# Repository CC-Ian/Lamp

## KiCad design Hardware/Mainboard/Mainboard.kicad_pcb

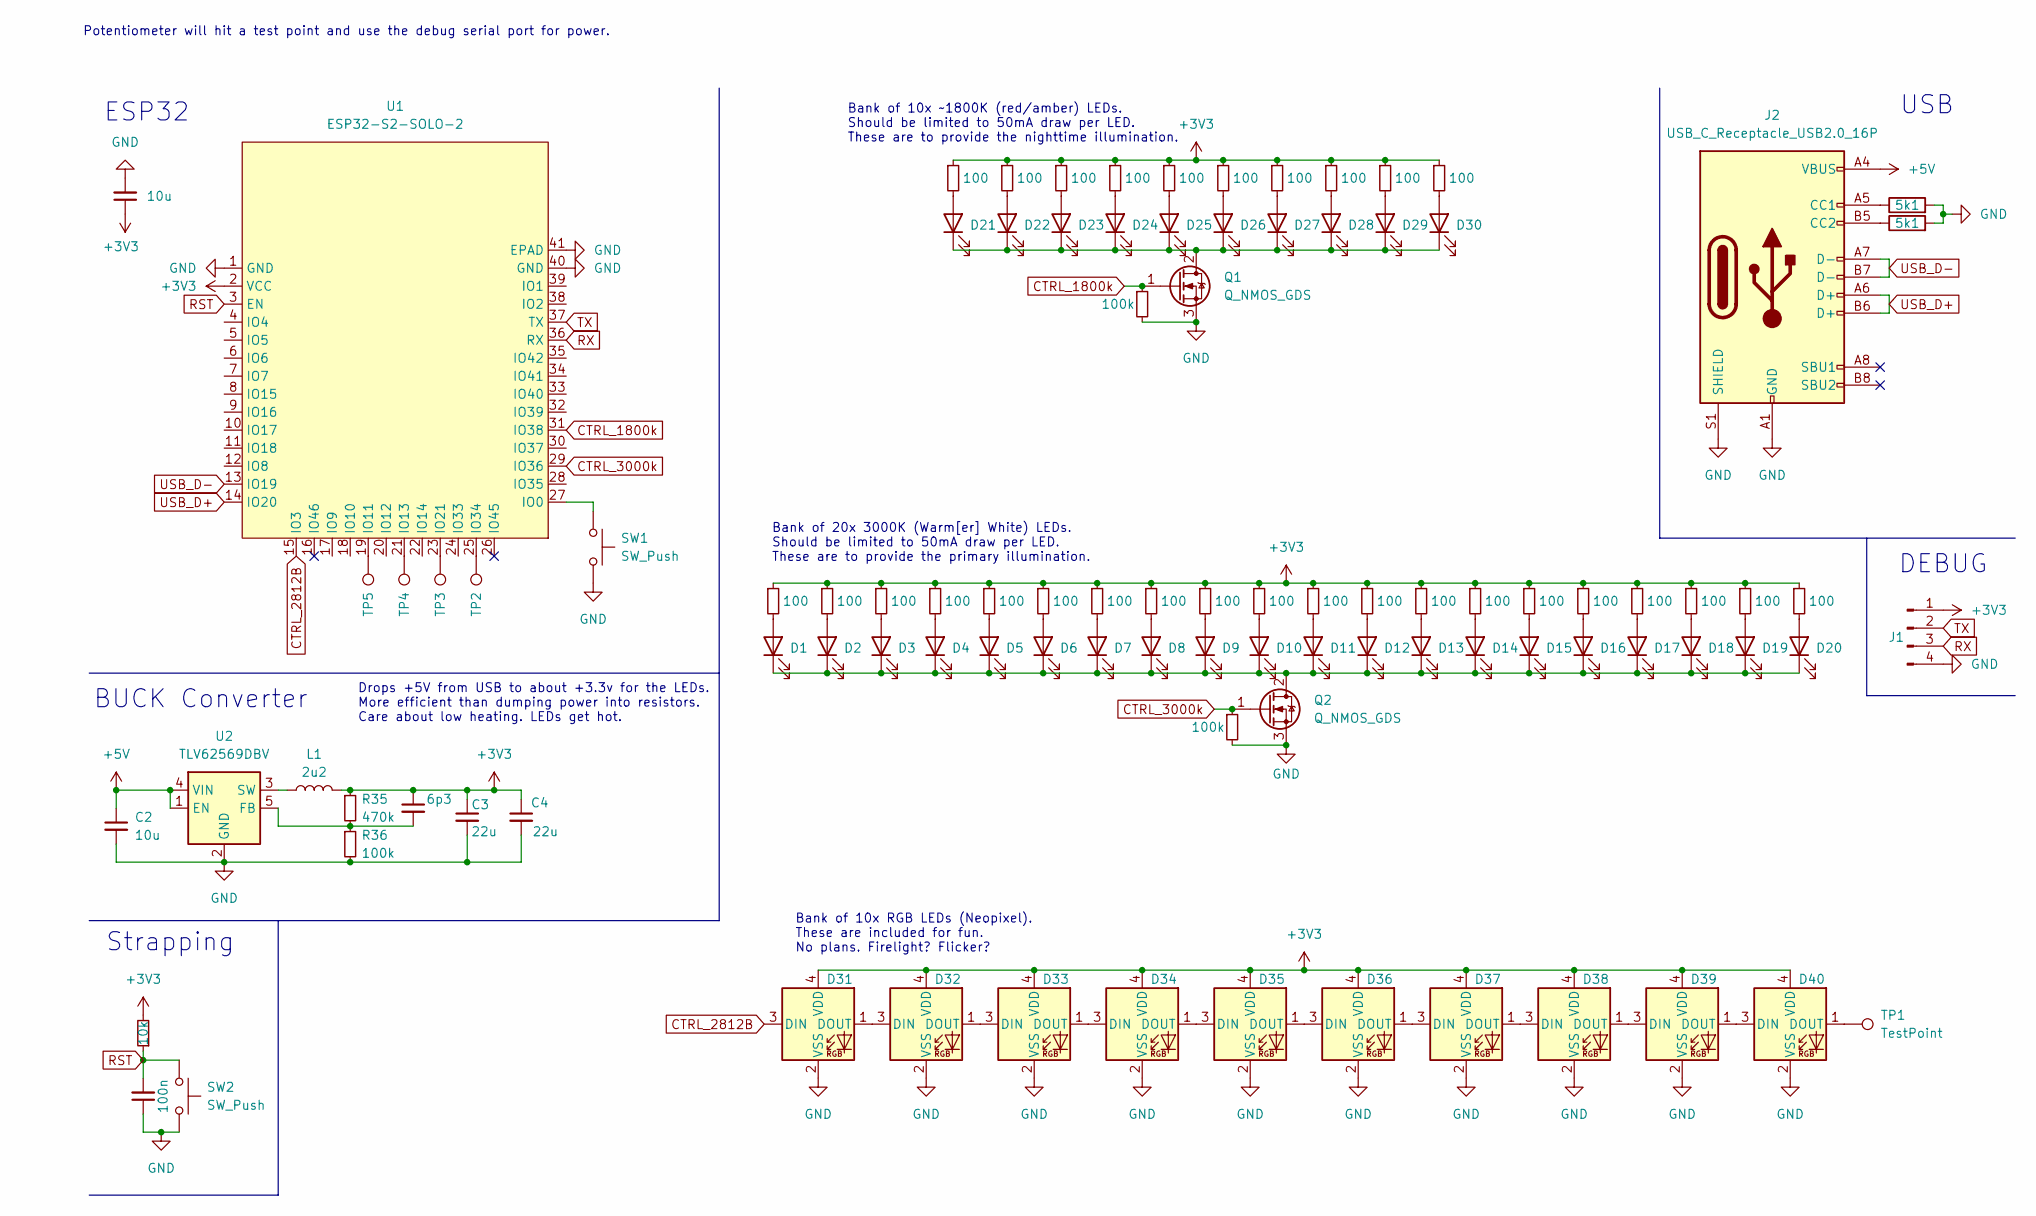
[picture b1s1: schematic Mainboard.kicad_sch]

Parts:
C1: 100n; C_0402_1005Metric
C2, C6: 10u; C_0603_1608Metric
C3, C4: 22u; C_0805_2012Metric
C5: 6p3; C_0402_1005Metric
D1, D2, D3, D4, D5, D6, D7, D8, D9, D10, D11, D12, D13, D14, D15, D16, D17, D18, D19, D20, D21, D22, D23, D24, D25, D26, D27, D28, D29, D30: LED; LED_PLCC_2835
D31, D32, D33, D34, D35, D36, D37, D38, D39, D40: WS2812B-2020; LED_WS2812B-2020_PLCC4_2.0x2.0mm
J1: Conn_01x04_Pin; PinHeader_1x04_P2.54mm_Vertical
J2: USB_C_Receptacle_USB2.0_16P; XKB_U263-14XN-5XQC14
L1: 2u2; L_Cenker_CKCS4018
Q1, Q2: Q_NMOS_GDS; TO-252-2
R1: 10k; R_0603_1608Metric
R2, R3: 5k1; R_0603_1608Metric
R4, R37: 100k; R_0603_1608Metric
R5, R6, R7, R8, R9, R10, R11, R12, R13, R14, R15, R16, R17, R18, R19, R20, R21, R22, R23, R24, R25, R26, R27, R28, R29, R30, R31, R32, R33, R34: 100; R_0603_1608Metric
R35: 470k; R_0402_1005Metric
R36: 100k; R_0402_1005Metric
SW1, SW2: SW_Push; SW_SPST_SKQG_WithStem
TP1: TestPoint; TestPoint_Pad_D1.0mm
TP2, TP3, TP4, TP5: TestPoint; TestPoint_Pad_D1.5mm
U1: ESP32-S2-SOLO-2; ESP32-S3-WROOM-1
U2: TLV62569DBV; SOT-23-5

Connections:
+3V3: C3.1, C4.1, C5.1, C6.1, D31.4 (VDD), D32.4 (VDD), D33.4 (VDD), D34.4 (VDD), D35.4 (VDD), D36.4 (VDD), D37.4 (VDD), D38.4 (VDD), D39.4 (VDD), D40.4 (VDD), J1.1, L1.2, R1.2, R5.1, R6.1, R7.1, R8.1, R9.1, R10.1, R11.1, R12.1, R13.1, R14.1, R15.1, R16.1, R17.1, R18.1, R19.1, R20.1, R21.1, R22.1, R23.1, R24.1, R25.1, R26.1, R27.1, R28.1, R29.1, R30.1, R31.1, R32.1, R33.1, R34.1, R35.1, U1.2 (VCC)
+5V: C2.1, J2.A4 (VBUS), J2.A9 (VBUS), J2.B4 (VBUS), J2.B9 (VBUS), U2.1 (EN), U2.4 (VIN)
CTRL_1800k: Q1.1 (G), R37.1, U1.31 (IO38)
CTRL_2812B: D31.3 (DIN), U1.15 (IO3)
CTRL_3000k: Q2.1 (G), R4.1, U1.29 (IO36)
GND: C1.1, C2.2, C3.2, C4.2, C6.2, D31.2 (VSS), D32.2 (VSS), D33.2 (VSS), D34.2 (VSS), D35.2 (VSS), D36.2 (VSS), D37.2 (VSS), D38.2 (VSS), D39.2 (VSS), D40.2 (VSS), J1.4, J2.A1 (GND), J2.A12 (GND), J2.B1 (GND), J2.B12 (GND), J2.S1 (SHIELD), Q1.3 (S), Q2.3 (S), R2.2, R3.2, R4.2, R36.2, R37.2, SW1.2, SW2.2, U1.1 (GND), U1.40 (GND), U1.41 (EPAD), U2.2 (GND)
unnamed: D1.2 (A), R5.2
unnamed: D1.1 (K), D2.1 (K), D3.1 (K), D4.1 (K), D5.1 (K), D6.1 (K), D7.1 (K), D8.1 (K), D9.1 (K), D10.1 (K), D11.1 (K), D12.1 (K), D13.1 (K), D14.1 (K), D15.1 (K), D16.1 (K), D17.1 (K), D18.1 (K), D19.1 (K), D20.1 (K), Q2.2 (D)
unnamed: D2.2 (A), R6.2
unnamed: D3.2 (A), R7.2
unnamed: D4.2 (A), R8.2
unnamed: D5.2 (A), R9.2
unnamed: D6.2 (A), R10.2
unnamed: D7.2 (A), R11.2
unnamed: D8.2 (A), R12.2
unnamed: D9.2 (A), R13.2
unnamed: D10.2 (A), R14.2
unnamed: D11.2 (A), R15.2
unnamed: D12.2 (A), R16.2
unnamed: D13.2 (A), R17.2
unnamed: D14.2 (A), R18.2
unnamed: D15.2 (A), R19.2
unnamed: D16.2 (A), R20.2
unnamed: D17.2 (A), R21.2
unnamed: D18.2 (A), R22.2
unnamed: D19.2 (A), R23.2
unnamed: D20.2 (A), R24.2
unnamed: D21.2 (A), R25.2
unnamed: D21.1 (K), D22.1 (K), D23.1 (K), D24.1 (K), D25.1 (K), D26.1 (K), D27.1 (K), D28.1 (K), D29.1 (K), D30.1 (K), Q1.2 (D)
unnamed: D22.2 (A), R26.2
unnamed: D23.2 (A), R27.2
unnamed: D24.2 (A), R28.2
unnamed: D25.2 (A), R29.2
unnamed: D26.2 (A), R30.2
unnamed: D27.2 (A), R31.2
unnamed: D28.2 (A), R32.2
unnamed: D29.2 (A), R33.2
unnamed: D30.2 (A), R34.2
unnamed: D31.1 (DOUT), D32.3 (DIN)
unnamed: D32.1 (DOUT), D33.3 (DIN)
unnamed: D33.1 (DOUT), D34.3 (DIN)
unnamed: D34.1 (DOUT), D35.3 (DIN)
unnamed: D35.1 (DOUT), D36.3 (DIN)
unnamed: D36.1 (DOUT), D37.3 (DIN)
unnamed: D37.1 (DOUT), D38.3 (DIN)
unnamed: D38.1 (DOUT), D39.3 (DIN)
unnamed: D39.1 (DOUT), D40.3 (DIN)
unnamed: D40.1 (DOUT), TP1.1
unnamed: J2.A5 (CC1), R2.1
unnamed: J2.B5 (CC2), R3.1
unnamed: SW1.1, U1.27 (IO0)
unnamed: TP5.1, U1.19 (IO11)
unnamed: TP4.1, U1.21 (IO13)
unnamed: TP3.1, U1.23 (IO21)
unnamed: TP2.1, U1.25 (IO34)
unnamed: C5.2, R35.2, R36.1, U2.5 (FB)
unnamed: L1.1, U2.3 (SW)
RST: C1.2, R1.1, SW2.1, U1.3 (EN)
RX: J1.3, U1.36 (RX)
TX: J1.2, U1.37 (TX)
USB_D+: J2.A6 (D+), J2.B6 (D+), U1.14 (IO20)
USB_D-: J2.A7 (D-), J2.B7 (D-), U1.13 (IO19)

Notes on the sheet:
Strapping
Drops +5V from USB to about +3.3v for the LEDs. More efficient than dumping power into resistors. Care about low heating. LEDs get hot.
Bank of 20x 3000K (Warm[er] White) LEDs. Should be limited to 50mA draw per LED. These are to provide the primary illumination.
USB
BUCK Converter
ESP32
DEBUG
Bank of 10x ~1800K (red/amber) LEDs. Should be limited to 50mA draw per LED. These are to provide the nighttime illumination.
Bank of 10x RGB LEDs (Neopixel). These are included for fun. No plans. Firelight? Flicker?
Potentiometer will hit a test point and use the debug serial port for power.

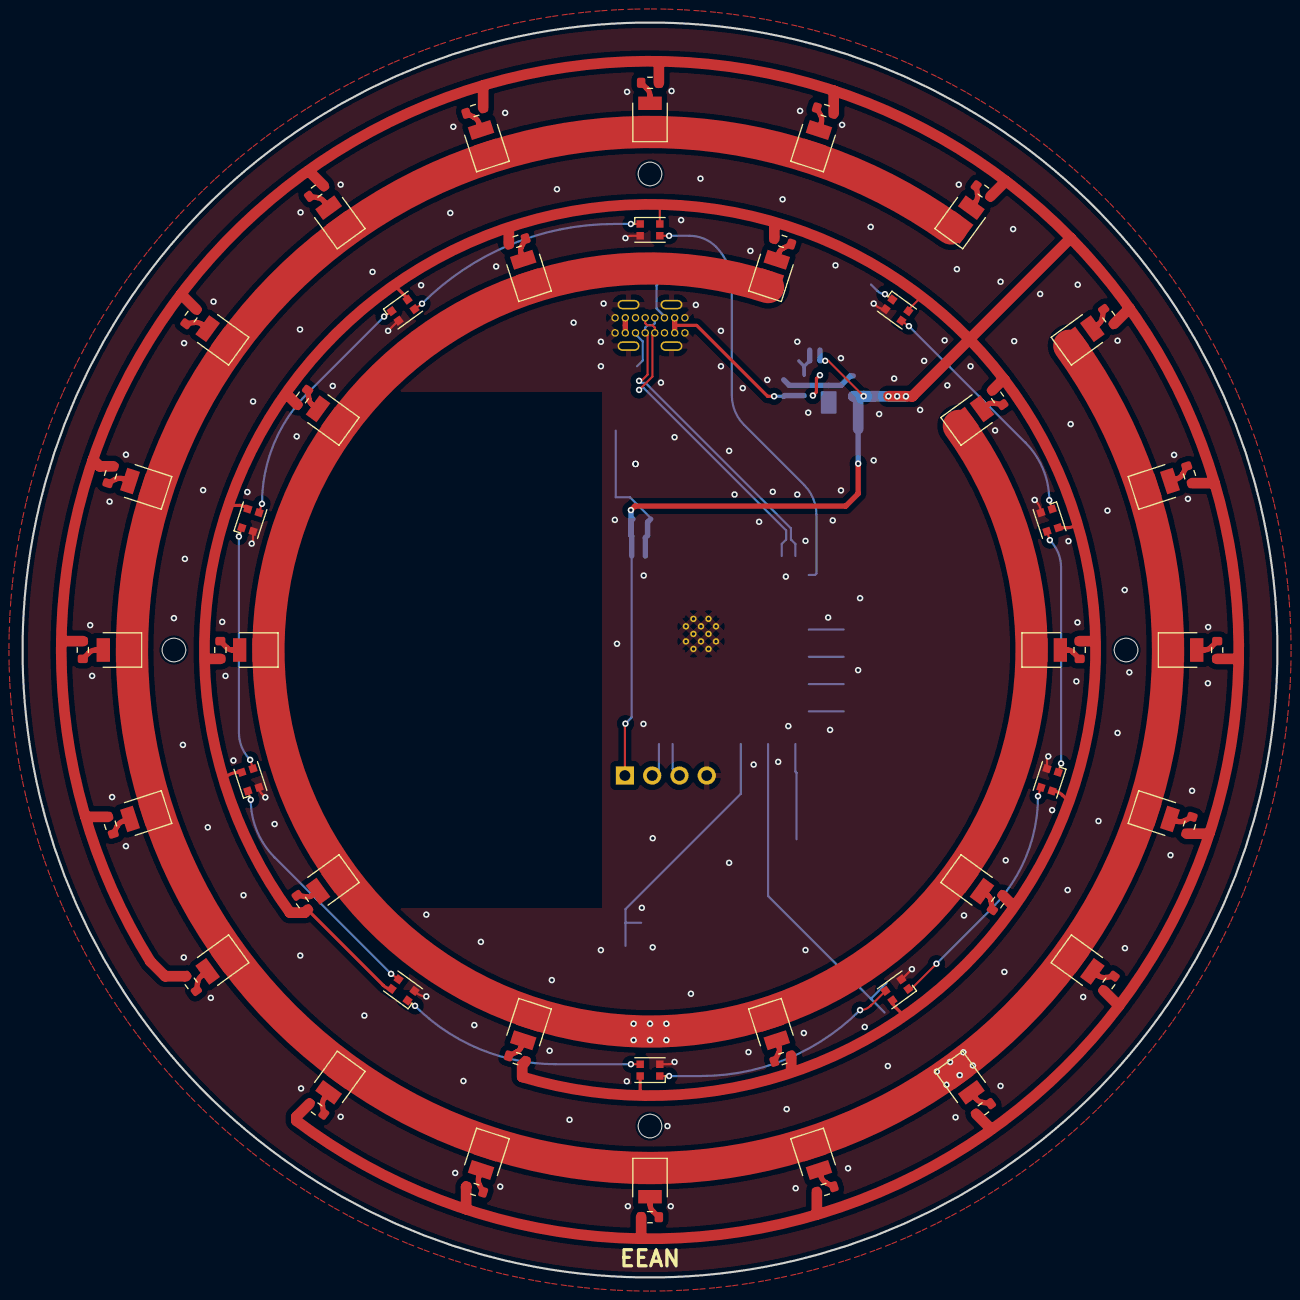
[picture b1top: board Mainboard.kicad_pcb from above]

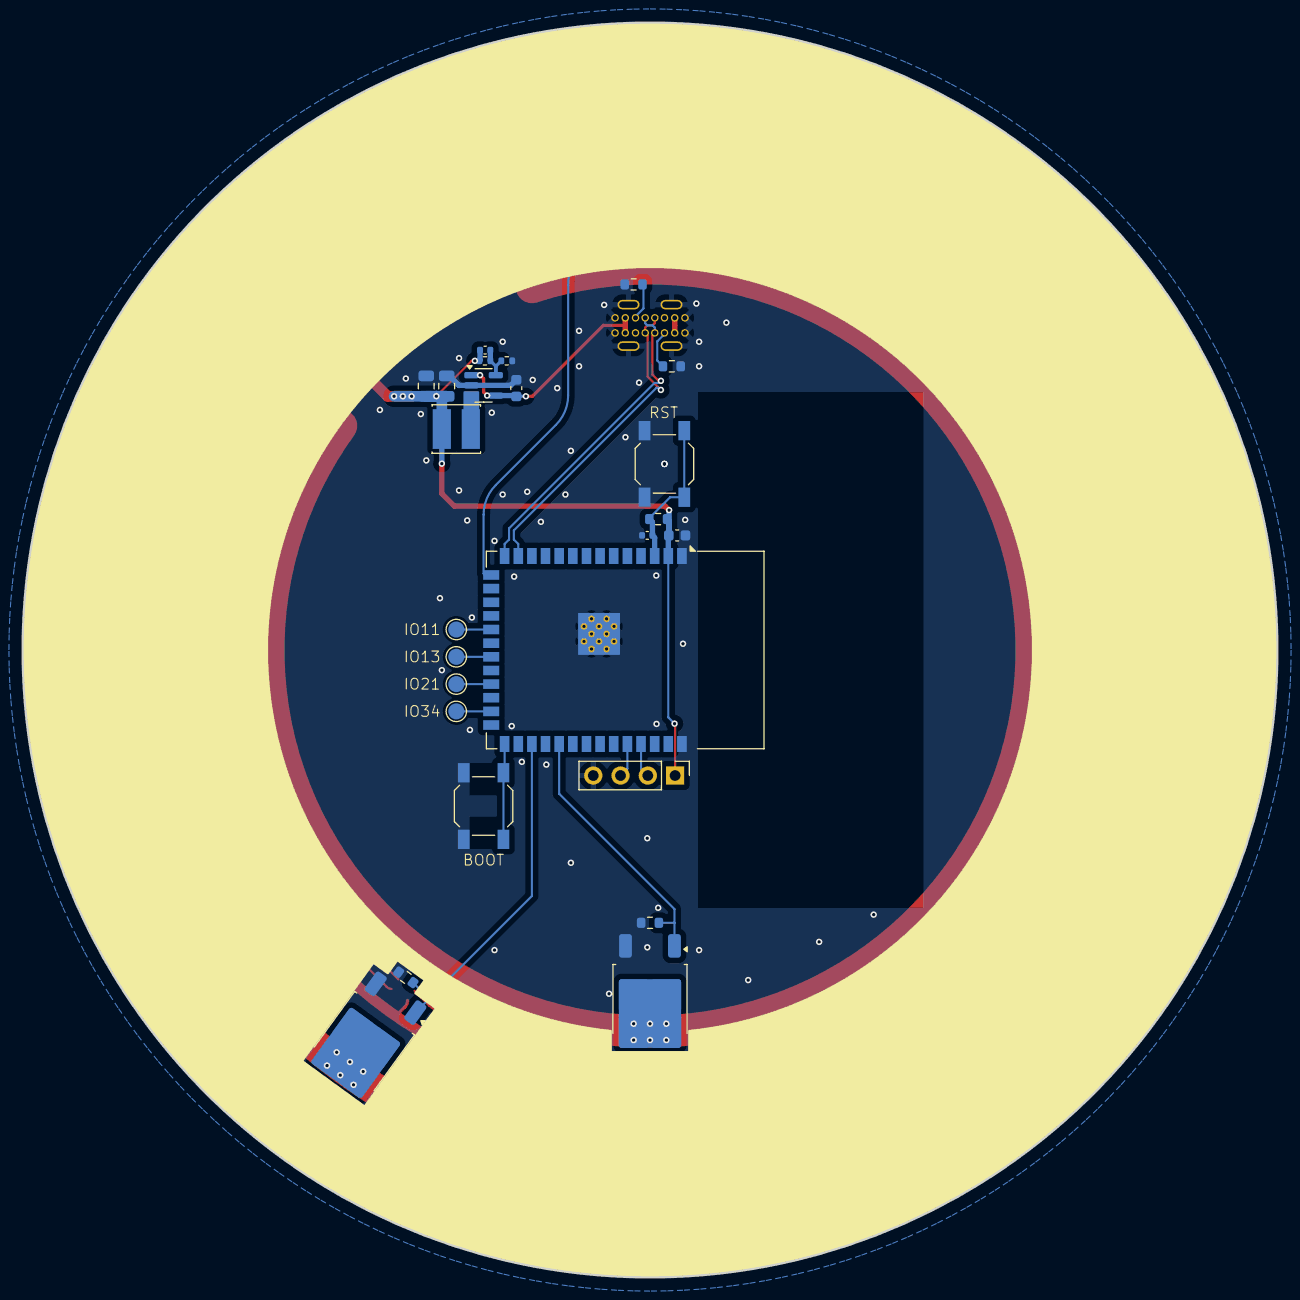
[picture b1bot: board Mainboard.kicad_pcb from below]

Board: 2 copper layers, 116.8 x 116.8 mm, 97 parts (27 on the bottom side), 62 nets.

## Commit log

2024-07-16 Technically should be a working schematic. Needs some more thought on power.
2024-07-20 Completed sample rev A. Requires Review.
2024-08-11 Finalize layout, silkscreen, outline. Pending review
